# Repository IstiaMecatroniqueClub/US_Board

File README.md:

# Istia Mecatronique Club - US Board

## Synopsis

This repository contains the source codes and the schematics of our US board. This board has an Ultra-Sound sensor and a CAN bus interface, controlled by an ATMega 32m1.

## Repository architecture

This repository contains a "board" folder with the schematics of the board, a "code" folder with the source code of the ATMega and a "documentation" folder with the doxygen documentation of the source code.

## The source code

### How does it work

The board waits for a remote request CAN message with the IDMSGCAN identifier (0x0C0), then returns a data CAN message with the same identifier and the sensor value (the distance over 2 bytes). Note that the board can also return an error value (if the returned distance is 0, 1 or 2 it means that an error occured).

### The files

The "code/include" folder contains 
 - a Pin interface class to handle a pin on the ATMega (this class sould not be instanciated)
 - an Input class to handle an input pin
 - an Ouput class to handle an output pin
 - a Led class to handle an led connected to the ATMega
 - a Hcrs04 class to handle the US sensor
 - a Timer class to handle timers in the ATMega

### The ATMega output.hex file
In the code folder you can find a Makefile to generate the binary *.hex file and upload it to the ATMega. The makefile is configured for
 - avrdude compiler ( $ sudo apt-get install avrdude avr-libc)
 - AVRispmkII programmer

Then do
 - $ make hex # to generate the binary ouput.hex
 - $ make upload # to upload the output.hex file to the ATMega
 - $ make all  # to compile and then upload 

This has been tester with Ubuntu and Lubuntu on a raspberry pi 3.

## The documentation
We use Doxygen to generate the documentation of the source code. By using the makefile (in the code folder) you can do
 - $ make documentation
To generate the documentation files.

Note that you need to have doxygen and graphviz (for the graphs) installed
 - $ sudo apt-get install doxygen
 - $ sudo apt-get install graphviz

## Tests

When powering the board, the LED should blink a few times and then stop.

## License

GNU General Public License v3.0.

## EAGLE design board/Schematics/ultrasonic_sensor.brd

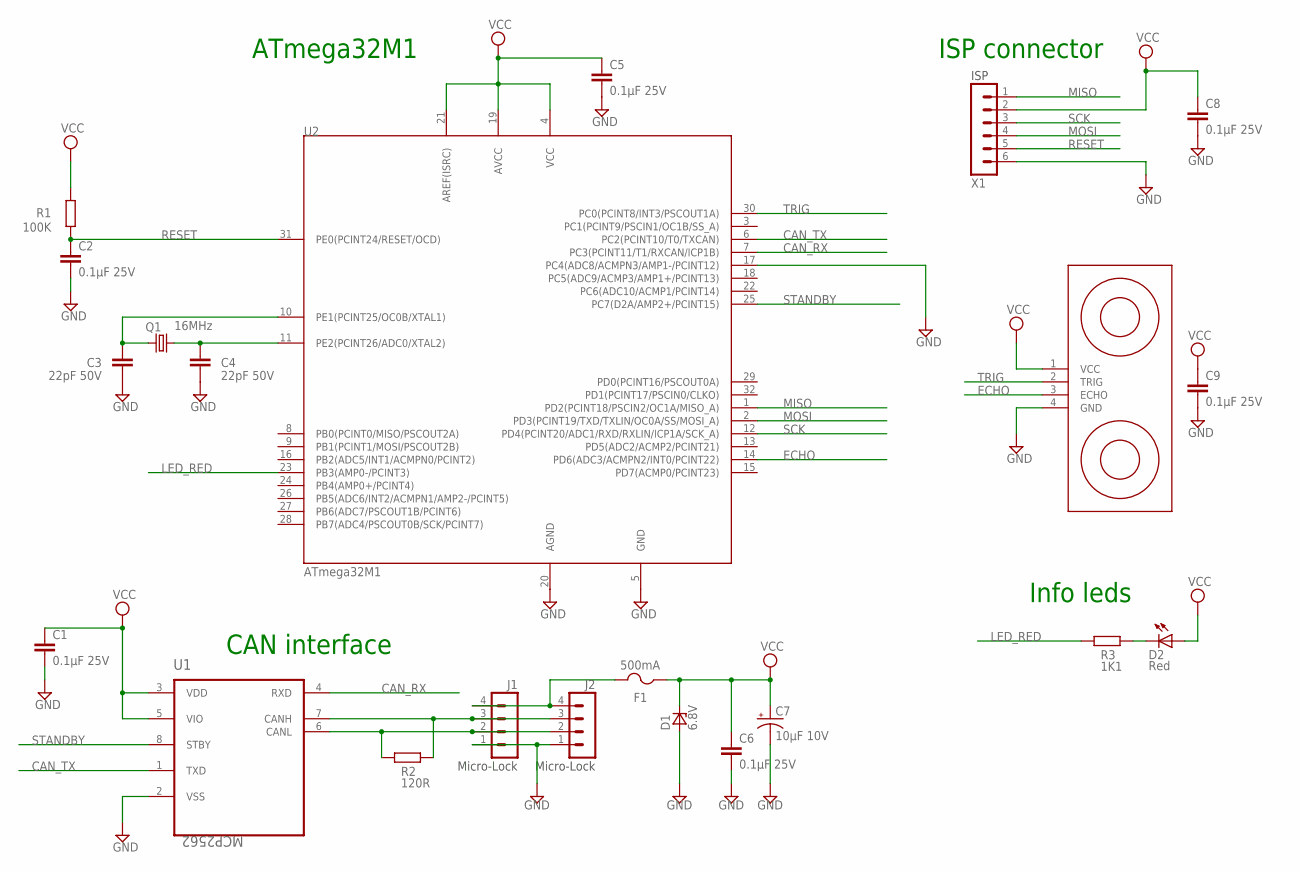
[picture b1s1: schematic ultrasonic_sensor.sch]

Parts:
C1, C2, C5, C6, C8, C9: 0.1µF 25V; C2012
C3, C4: 22pF 50V; C2012
C7: 10µF 10V; EIA3216
D1: 6.8V; DO-214AA
D2: Red; VLD
F1: 500mA; EIARS-481-2
J1, J2: Micro-Lock; 504195-0470
Q1: 16MHz; SMD_KX7
R1: 100K; R2012
R2: 120R; R2012
R3: 1K1; R2012
U1: MCP2562; SOIC8
U2: ATmega32M1; TQFP32
U3: HC-SR04; ULTRASONIC-HC-SR04
X1: ISP; MINITEK_127_6WAY_SMD

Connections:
CAN_RX: U1.4 (RXD), U2.7 (PC3(PCINT11/T1/RXCAN/ICP1B))
CAN_TX: U1.1 (TXD), U2.6 (PC2(PCINT10/T0/TXCAN))
ECHO: U2.14 (PD6(ADC3/ACMPN2/INT0/PCINT22)), U3.3 (ECHO)
GND: C1.2, C2.2, C3.2, C4.2, C5.2, C6.2, C7.C (-), C8.2, C9.2, D1.A, J1.1, J2.1, U1.2 (VSS), U2.5 (GND), U2.17 (PC4(ADC8/ACMPN3/AMP1-/PCINT12)), U2.20 (AGND), U3.4 (GND), X1.6
LED_RED: R3.2, U2.23 (PB3(AMP0-/PCINT3))
MISO: U2.1 (PD2(PCINT18/PSCIN2/OC1A/MISO_A)), X1.1
MOSI: U2.2 (PD3(PCINT19/TXD/TXLIN/OC0A/SS/MOSI_A)), X1.4
unnamed: D2.C, R3.1
unnamed: F1.2, J1.4, J2.4
unnamed: J1.2, J2.2, R2.2, U1.6 (CANL)
unnamed: J1.3, J2.3, R2.1, U1.7 (CANH)
unnamed: C4.1, Q1.3 (2), U2.11 (PE2(PCINT26/ADC0/XTAL2))
unnamed: C3.1, Q1.1, U2.10 (PE1(PCINT25/OC0B/XTAL1))
RESET: C2.1, R1.1, U2.31 (PE0(PCINT24/RESET/OCD)), X1.5
SCK: U2.12 (PD4(PCINT20/ADC1/RXD/RXLIN/ICP1A/SCK_A)), X1.3
STANDBY: U1.8 (STBY), U2.25 (PC7(D2A/AMP2+/PCINT15))
TRIG: U2.30 (PC0(PCINT8/INT3/PSCOUT1A)), U3.2 (TRIG)
VCC: C1.1, C5.1, C6.1, C7.A (+), C8.1, C9.1, D1.C, D2.A, F1.1, R1.2, U1.3 (VDD), U1.5 (VIO), U2.4 (VCC), U2.19 (AVCC), U2.21 (AREF(ISRC)), U3.1 (VCC), X1.2

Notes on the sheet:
ISP connector
Info leds
CAN interface
ATmega32M1

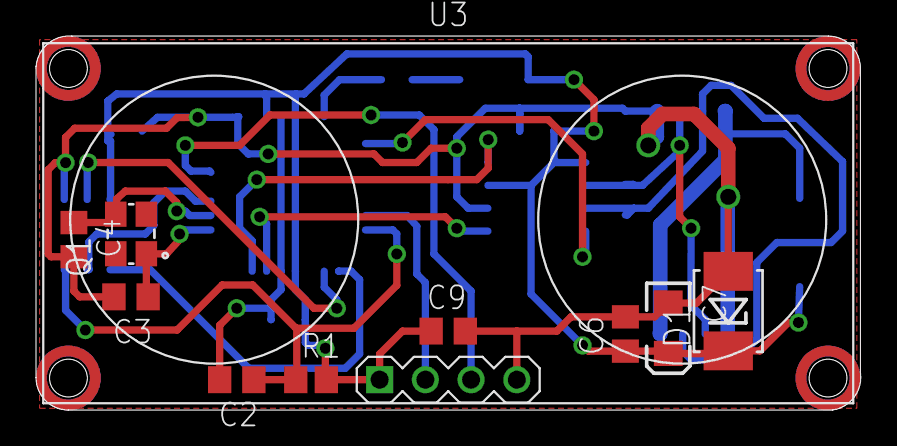
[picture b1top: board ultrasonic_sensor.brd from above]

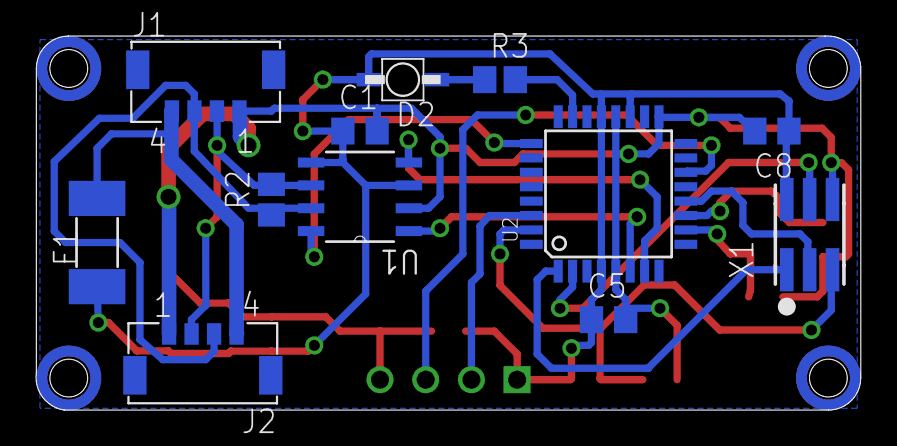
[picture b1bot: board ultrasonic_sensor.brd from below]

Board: 2 copper layers, 45.8 x 20.8 mm, 23 parts (12 on the bottom side), 18 nets.

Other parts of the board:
DRILEGEND: DRILEGEND

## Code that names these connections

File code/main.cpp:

//! \file main.cpp
//! \brief Main file
//! \author Baptiste Hamard,Franck Mercier, Remy Guyonneau
//! \date 2017 04 24
//!
//! Main file for the US card. To change the Ultra Sound identifier, just change the IDMSCAN constant before generating the .hex file.
#define FOSC           16000
#define F_CPU          16000000UL

#include <avr/io.h>
#include <avr/interrupt.h>
#include "hcsr04.h"
#include "led.h"

// Configuration declaration for the LED wiring
#define LED_RED_PORT PORTB //!< The ATMega port where the red LED is wired
#define LED_RED_PIN  3     //!< The ATMega pin where the red LED is wired
#define LED_RED_POL  0     //!< The polarity of the red LED


// Configuration declaration for the LED wiring
#define US_TRIG_PORT    PORTC //!< The ATMega port where the trigger of the US is wired
#define US_TRIG_PIN     0     //!< The ATMega port where the trigger of the US is wired
#define US_ECHO_PORT    PORTD //!< The ATMega port where the echo of the US is wired
#define US_ECHO_PIN     6     //!< The ATMega port where the echo of the US is wired


#define IDMSGCAN 0x0C0 //!< the identifier of the US card

//! \fn void initCANBus()
//! \brief Intialize the CAN Bus.
//!
//! Function that initializes the CANBus according to the wiring and the needed speed (500kb/s).
//! It also enable the CAN module interruptions
void initCANBus(){
	// Enable of CAN transmit
	DDRC|=0x80; // Configuration of the standby pin as an output
	// (for a transceiver MCP2562 with the stby pin wired to the uC PC7)
	// Enable the MCP2562 (STANDBY to 0)
	PORTC &= 0x7F; // Activation of the MCP2562
	// (for a transceiver MCP2562 with the stby pin wired to the uC PC7)

	// Initialization of CAN module
	CANGCON  = (1 << SWRES); // Reset CAN module
	CANGCON  = 0x02; // Enable CAN module

	CANBT1 = 0x06; // Speed Config (500kb/s)
	CANBT2 = 0x04;
	CANBT3 = 0x13;

	CANHPMOB = 0x00; // No priority between the CAN MOB

	// Enable CAN interruptions and especially reception interruptions
	CANGIE |= 0xA0;
}

//! \fn void initCANMOB()
//! \brief Intialize the CAN MOB.
//!
//! Intialize the CAN MOB. A MOB can be seen as a "CAN socket".
//! In this case the MOB1 is used to receive remote request
//! and MOB0 is used to send the Ultra sound value
void initCANMOB(){
	CANPAGE = 0x10; // selection of MOB1 (reveice request)

	CANIDT4 = 0x04; // Config as reception remote (rtr = 1)
	CANIDT3 = 0x00;
	CANIDT2 = (uint8_t)( (IDMSGCAN & 0x00F)<< 5 ); // using the constant to configure the remote request identifier
	CANIDT1 = (uint8_t)( IDMSGCAN >> 3 );

	CANIDM4 = 0x04; // mask over the rtr value
	CANIDM3 = 0xFF; // mask over the identifier (we only want an interruption if the received CAN message is a remote request with the corresponding identifier)
	CANIDM2 = 0xFF;
	CANIDM1 = 0xFF;

	CANCDMOB = 0x80; // Config MOB as reception
	
	CANIE2 = 0x02; // enable the interruptions over the MOB 1

	sei(); // set enable interruption
}

Hcsr04 us_sensor(Output(&US_TRIG_PORT, US_TRIG_PIN), Input(&US_ECHO_PORT, US_ECHO_PIN)); //!< The Ultra Sound Sensor
Led led(&LED_RED_PORT, LED_RED_PIN, LED_RED_POL); //!< The RED Led

int main(void) {
	for(int i=0; i<4; i++){
		led.blink(100);
	}

	initCANBus(); // intialization of the CAN Bus
	initCANMOB(); // intialization of the CAN MOB

	while(1){
	}
}


//! \fn ISR(CAN_INT_vect)
//! \brief CAN interruption.
//! This function is called when an CAN interruption is raised.
//! When it appens, the US sensor value is readed and sent using the MOB 0
ISR(CAN_INT_vect){
	cli(); // disable the interruption (no to be disturbed when dealing with one)

	led.blink(50); // blink the LED

	CANPAGE = 0x10; // Selection of MOB 1
	CANSTMOB = 0x00; // Reset the status of the MOB
	CANCDMOB = 0x80; // Config as reception MOB
	CANIE2 = 0x02; // Enable the interuption over MOB 1 (for the next one)

	uint16_t dst = us_sensor.getDistance(); // get the distance of the Ultra Sound Sensor

	CANPAGE  = 0x00; //Selection of MOB 0

	CANIDT4 = 0x00; // Config as data (rtr = 0)
	CANIDT3 = 0x00;
	CANIDT2 = (uint8_t)( (IDMSGCAN & 0x00F)<< 5 ); // use the same identifier as the remote request
	CANIDT1 = (uint8_t)( IDMSGCAN >> 3 );

	CANMSG = (uint8_t)( (dst & 0xFF00) >> 8 ); // update the first byte of the CAN message data
	CANPAGE = 0x01; // move to next index for CANMSG (canpage : MOB|INDEX) (next byte of the data)
	CANMSG = (uint8_t)( dst & 0x00FF ); // update the second byte of the CAN message data

	CANCDMOB = 0x42; // send the message using the MOB 0

	sei(); // enable the interruptions
}

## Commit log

2017-06-15 coucou
2017-06-15 Adding Board folder
2017-06-15 Adding source code
2017-06-16 update readme file
